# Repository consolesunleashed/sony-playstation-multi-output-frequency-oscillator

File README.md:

Working on designs to release for free can be both time consuming and expensive. If you like what I do, a small donation will go a long way in helping me continue to serve the modding community as best as I can, with many more free and original guides, designs, and ideas to come.

# Sony PlayStation Multi Output Frequency Oscillator (MOFO)

The multi output frequency oscillator (MOFO) is a dual clock mod for the Sony PlayStation that provides a switchable PAL/NTSC GPU clock and PAL/NTSC RGB Encoder subcarrier clock, as well as a fixed subcarrier clock for PAL60 operation.

## What is the difference between a DFO, MFO, and MOFO?

- The Dual Frequency Oscillator (DFO) provides an auto switching GPU clock output.
- The Multi Frequency Oscillator (MFO) provides an auto switching GPU clock output and an auto switching subcarrier clock output.
- The Multi Output Frequency Oscillator (MOFO) provides an auto switching GPU clock output, an auto switching subcarrier clock output, and an additional fixed subcarrier clock output.

The MOFO is an updated version of the MFO which itself was an updated version of the DFO.

## Composite Video & Single Format TV's

One reason I wanted to design this mod is because I own a single format PAL CRT TV and have been wanting to play Silent Hill in 60Hz via composite video. This results in a black and white image so I would be forced to use RGB or play in 50Hz. Neither of which appeals to me for Silent Hill. So I designed the MOFO.

As you can see by the screenshot, this is a 60Hz image, in colour, and with the correct fog effect over composite video. Thanks to the MOFO's SUB-B clock output, I get a PAL60 signal which my PAL only CRT TV can understand.

## PAL60 & Composite Video Dot Crawl

PAL60 will be prone to the same problems as any standalone PAL60 mod such as dot crawl. The MOFO does not eliminate dot crawl, it is simply a convenient way to generate a PAL60 signal for those that require this mod. However, this may be more in sync and less problematic than standalone PAL60 mods because the clocks are atleast derived from the same clock source.

## Compatibility

PU-8 / PU-18

- GPU output is necessary for correct GPU clock in 50Hz and 60Hz console modes.
- Sub-A output is not necessary because the GPU creates the correct PAL & NTSC subcarrier clocks in all regions.
- Sub-B output can be used to force PAL60 operation for use with TVs that are incompatible with NTSC signals.

PU-20 / PU-22 / PU-23 / PM-41

- GPU output is necessary for correct GPU clock in 50Hz and 60Hz console modes.
- Sub-A output is necessary to get correct PAL & NTSC subcarrier clocks in all regions.
- Sub-B output can be used to force PAL60 operation for use with TVs that are incompatible with NTSC signals.

## Recommended Dual Clock Mod

PU-8 / PU-18

- If using RGB = DFO (or MOFO using GPU clock output only)
- If using composite video & a dual format PAL/NTSC TV = DFO (or MOFO using GPU clock output only)
- If using composite video & a single format TV = MOFO (GPU clock output & Sub-B clock output)

PU-20 / PU-22 / PU-23 / PM-41

- If using RGB = DFO (or MOFO using GPU clock output only)
- If using composite video & a dual format PAL/NTSC TV = MOFO (GPU clock output & Sub-A clock output)
- If using composite video & a single format TV = MOFO (GPU clock output & Sub-B clock output)

## Manufacturing

Nothing special. 1mm PCB is fine.

## Version History

- MOFO v1 - 06/05/2023

## Future Work

- Ability to switch between the standard subcarrier output (SUB-A) or the PAL60 subcarrier output (SUB-B).

## License

If you use this in any way, shape or form, you must include a link back to this repository and mention me by name on any sales pages and social media posts. Not only will this help me to keep designing mod kits and offering them to the community, but it is basic common courtesy as well. Don't be a douchebag. :)

Also this 'GNU GENERAL PUBLIC LICENSE Version 2, June 1991'.

## Donate

Working on designs to release for free can be both time consuming and expensive. If you like what I do, a small donation will go a long way in helping me continue to serve the modding community as best as I can, with many more free and original guides, designs, and ideas to come.

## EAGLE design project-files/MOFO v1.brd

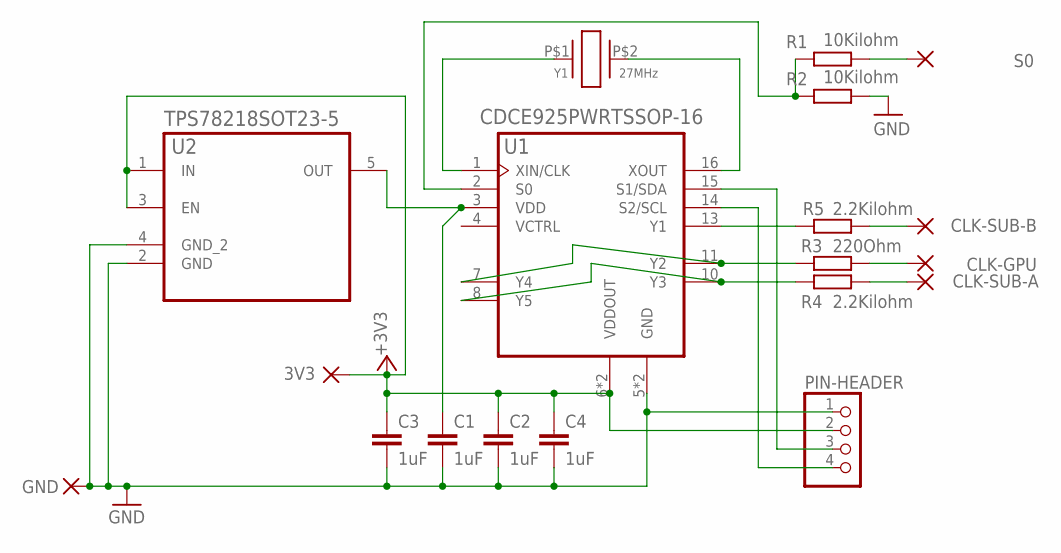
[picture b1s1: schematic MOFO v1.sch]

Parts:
3V3: PADSCIRCLE-1,5X1,5; CIRCLE-1,5X1,5
C1, C2, C3, C4: 1uF; C0603
CLK-GPU: PADSCIRCLE-1,5X1,5; CIRCLE-1,5X1,5
CLK-SUB-A: PADSCIRCLE-1,5X1,5; CIRCLE-1,5X1,5
CLK-SUB-B: PADSCIRCLE-1,5X1,5; CIRCLE-1,5X1,5
GND: PADSCIRCLE-1,5X1,5; CIRCLE-1,5X1,5
PIN-HEADER: PIN-HEADER-1X4PH-1X04M; PH-1X04M
R1, R2: 10Kilohm; R0603
R3: 220Ohm; R0603
R4, R5: 2.2Kilohm; R0603
S0: PADSCIRCLE-1,5X1,5; CIRCLE-1,5X1,5
U1: CDCE925PWRTSSOP-16; TSSOP-16
U2: TPS78218SOT23-5; SOT23-5
Y1: 27MHz; ABM3

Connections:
+1.8V: C1.1, U1.3 (VDD), U2.5 (OUT)
+3.3V: 3V3.1, C2.1, C3.1, C4.1, PIN-HEADER.2, U1.6 (VDDOUT), U1.9 (VDDOUT), U2.1 (IN), U2.3 (EN)
CLK-GPU-1: R3.1, U1.7 (Y4), U1.11 (Y2)
CLK-GPU-2: CLK-GPU.1, R3.2
CLK-SUB-A-1: R4.1, U1.8 (Y5), U1.10 (Y3)
CLK-SUB-A-2: CLK-SUB-A.1, R4.2
CLK-SUB-B-1: R5.1, U1.13 (Y1)
CLK-SUB-B-2: CLK-SUB-B.1, R5.2
GND: C1.2, C2.2, C3.2, C4.2, GND.1, PIN-HEADER.1, R2.2, U1.5 (GND), U1.12 (GND), U2.2 (GND), U2.4 (GND_2)
S0-1: R1.1, R2.1, U1.2 (S0)
S0-2: R1.2, S0.1
SCL: PIN-HEADER.4, U1.14 (S2/SCL)
SDA: PIN-HEADER.3, U1.15 (S1/SDA)
X1: U1.1 (XIN/CLK), Y1.P$1 (1)
X2: U1.16 (XOUT), Y1.P$2 (2)

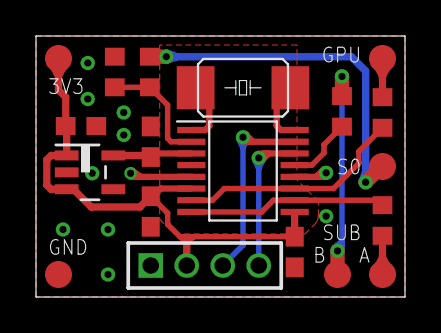
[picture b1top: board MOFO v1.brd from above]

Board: 2 copper layers, 20.5 x 14.5 mm, 19 parts (0 on the bottom side), 15 nets.

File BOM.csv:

Part,MPN,Value,Case/Size,Amount,Digikey,Mouser,Farnell
Programmable Clock Synthesizer,CDCE925PWR,CDCE925PWR,TSSOP-16,1,296-41230-1-ND,595-CDCE925PWR,
Capacitor,,1uF / 25V,0603,4,,,
Resistor,,2.2Kilohm,0603,2,,,
Resistor,,220Ohm,0603,1,,,
Resistor,,10Kilohm,0603,2,,,
Crystal,445I23D27M00000,27MHz / 18pF,,1,CTX1176CT-ND,774-445I23D27M00000,
Voltage Regulator,TPS78218DDCR,1.8V / 150mA,SOT-23-5,1,296-40962-1-ND,595-TPS78218DDCR,
